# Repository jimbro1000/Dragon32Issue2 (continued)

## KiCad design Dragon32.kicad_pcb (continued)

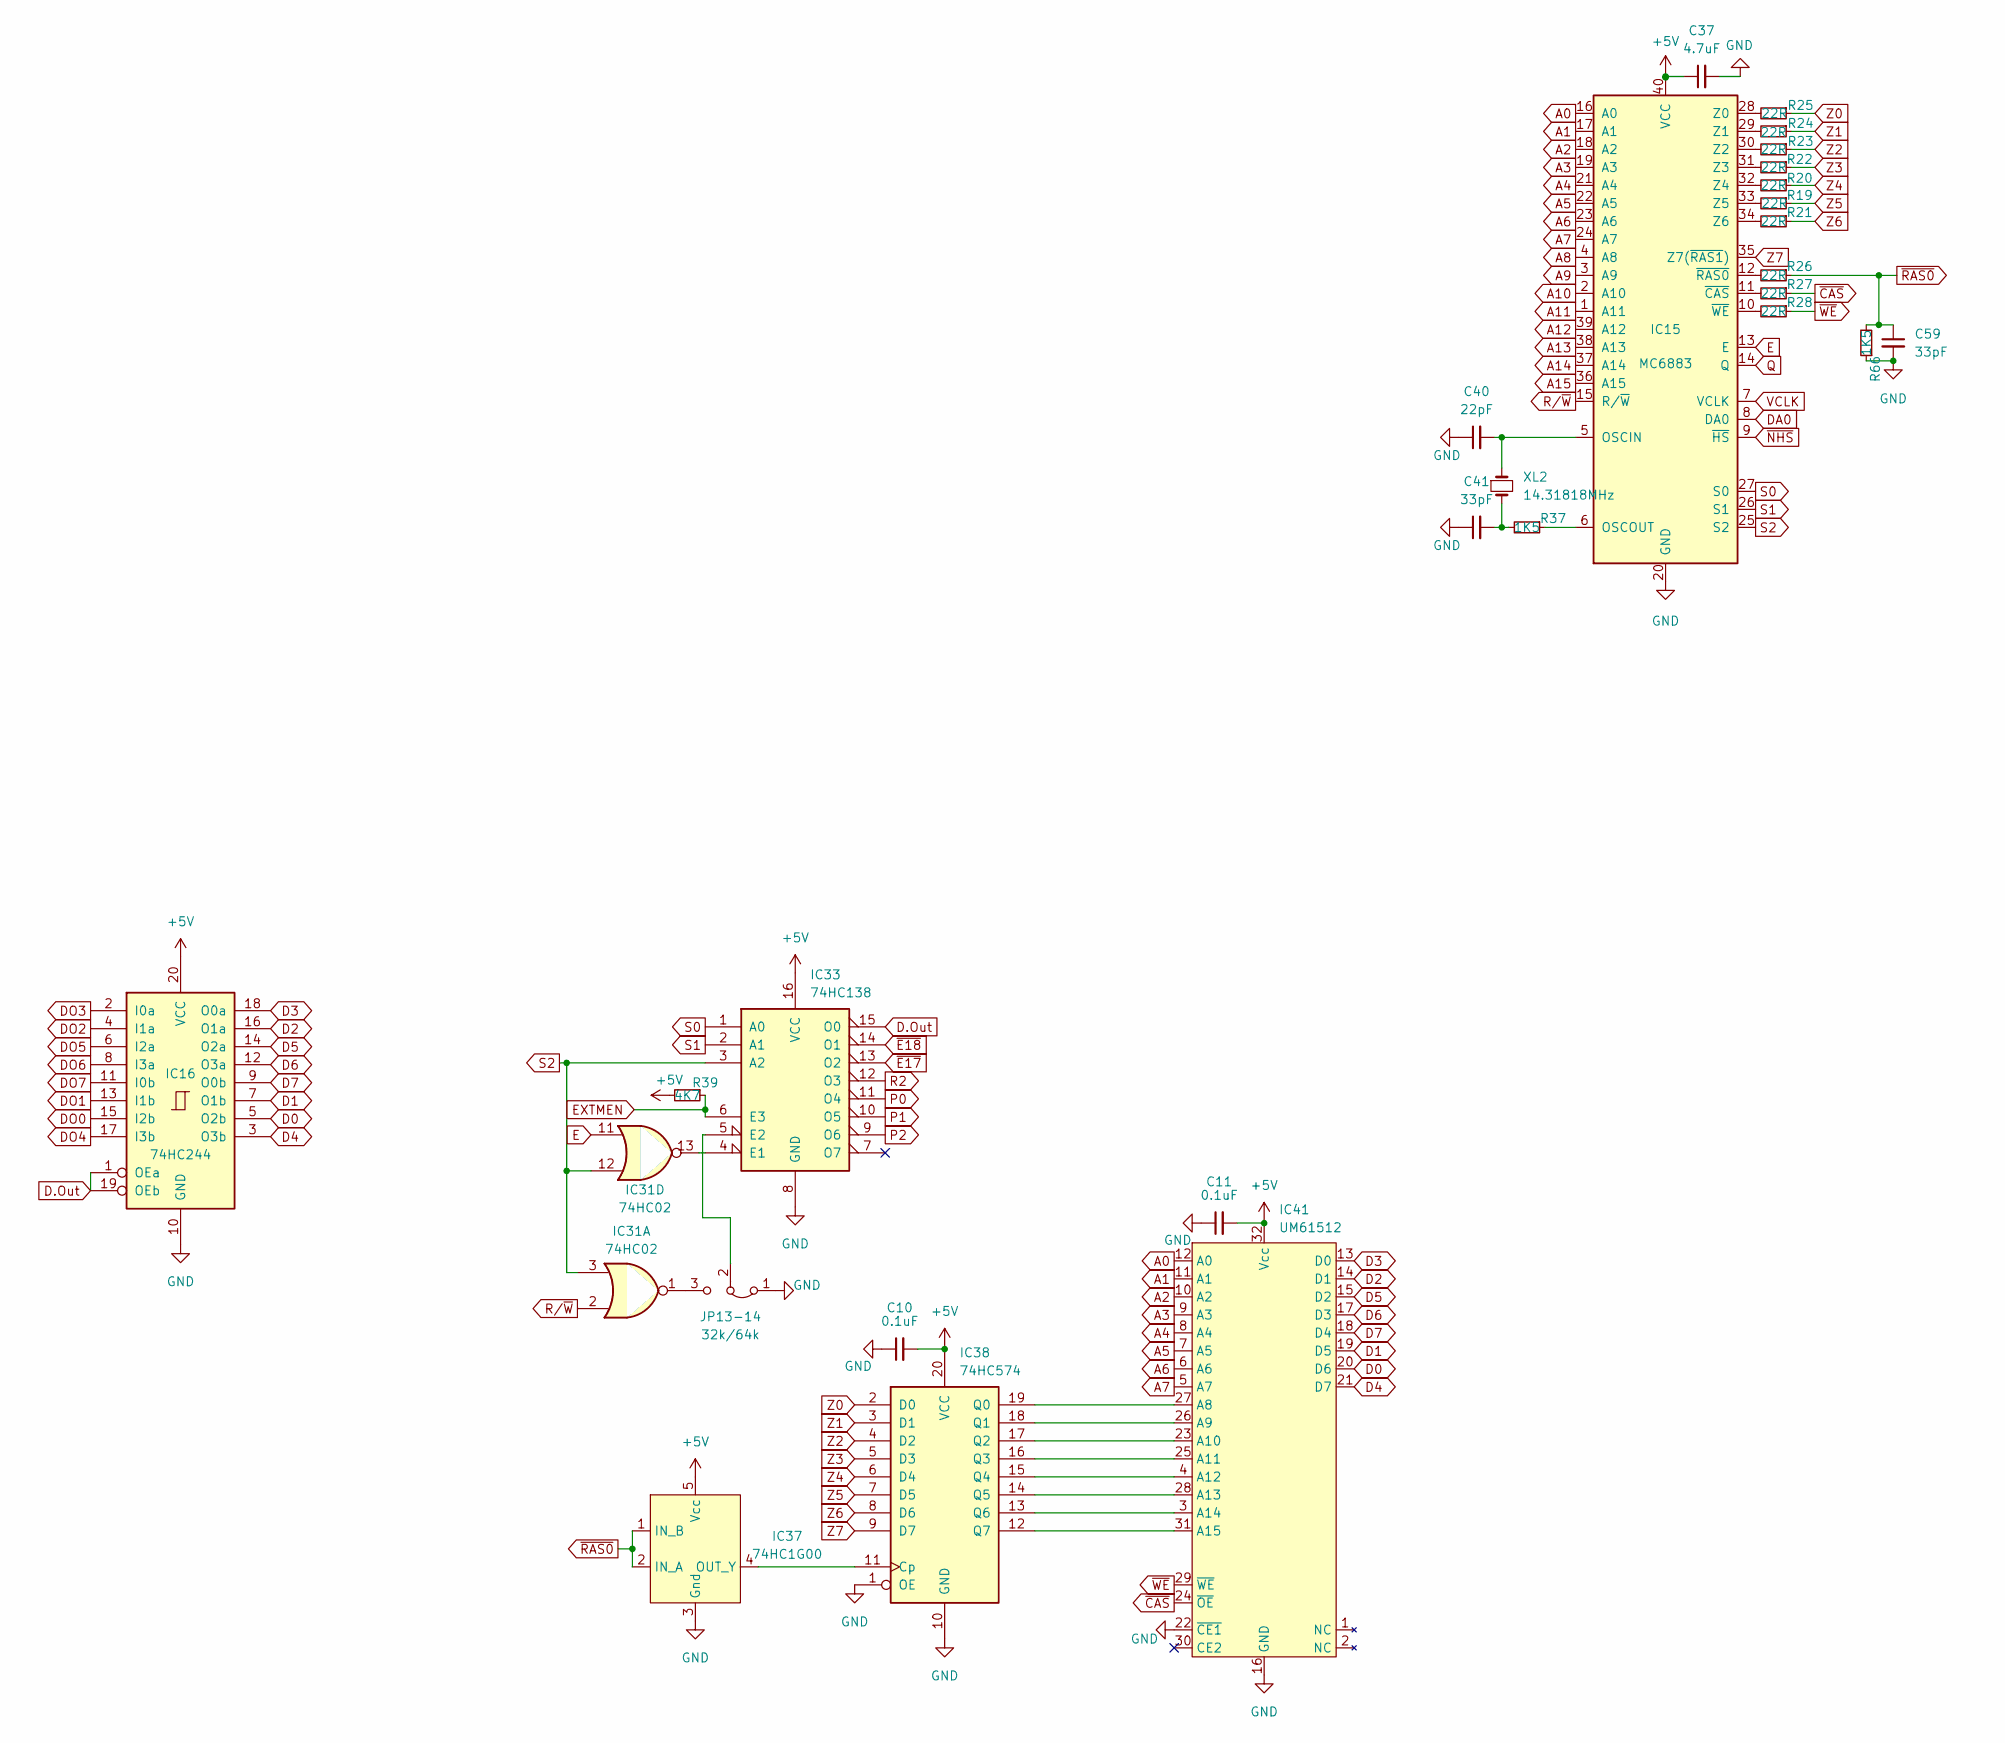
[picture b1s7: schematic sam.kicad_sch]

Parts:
C10, C11: 0.1uF; C_0805_2012Metric
C37: 4.7uF; C_0805_2012Metric
C40: 22pF; C_0805_2012Metric
C41, C59: 33pF; C_0805_2012Metric
IC15: MC6883; DIP-40_W15.24mm
IC16: 74HC244; SOIC-20W_7.5x12.8mm_P1.27mm
IC31: 74HC02; SOIC-14_3.9x8.7mm_P1.27mm
IC33: 74HC138; SOIC-16_3.9x9.9mm_P1.27mm
IC37: 74HC1G00; TSOP-5_1.65x3.05mm_P0.95mm
IC38: 74HC574; SOIC-20W_7.5x12.8mm_P1.27mm
IC41: UM61512; DIP-32_W7.62mm
JP13-14: 32k/64k; PinHeader_1x03_P2.54mm_Vertical
R19, R20, R21, R22, R23, R24, R25, R26, R27, R28: 22R; R_0805_2012Metric
R37, R66: 1K5; R_0805_2012Metric
R39: 4K7; R_0805_2012Metric
XL2: 14.31818MHz; Crystal_HC18-U_Horizontal

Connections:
+5V: C10.2, C11.2, C37.1, IC15.40 (VCC), IC16.20 (VCC), IC33.16 (VCC), IC37.5 (Vcc), IC38.20 (VCC), IC41.32 (Vcc), R39.2; also elsewhere on the board
A0: IC15.16 (A0), IC41.12 (A0); also elsewhere on the board
A1: IC15.17 (A1), IC41.11 (A1); also elsewhere on the board
A2: IC15.18 (A2), IC41.10 (A2); also elsewhere on the board
A3: IC15.19 (A3), IC41.9 (A3); also elsewhere on the board
A4: IC15.21 (A4), IC41.8 (A4); also elsewhere on the board
A5: IC15.22 (A5), IC41.7 (A5); also elsewhere on the board
A6: IC15.23 (A6), IC41.6 (A6); also elsewhere on the board
A7: IC15.24 (A7), IC41.5 (A7); also elsewhere on the board
A8: IC15.4 (A8); also elsewhere on the board
A9: IC15.3 (A9); also elsewhere on the board
A10: IC15.2 (A10); also elsewhere on the board
A11: IC15.1 (A11); also elsewhere on the board
A12: IC15.39 (A12); also elsewhere on the board
A13: IC15.38 (A13); also elsewhere on the board
A14: IC15.37 (A14); also elsewhere on the board
A15: IC15.36 (A15); also elsewhere on the board
D0: IC16.5 (O2b), IC41.20 (D6); also elsewhere on the board
D1: IC16.7 (O1b), IC41.19 (D5); also elsewhere on the board
D2: IC16.16 (O1a), IC41.14 (D1); also elsewhere on the board
D3: IC16.18 (O0a), IC41.13 (D0); also elsewhere on the board
D4: IC16.3 (O3b), IC41.21 (D7); also elsewhere on the board
D5: IC16.14 (O2a), IC41.15 (D2); also elsewhere on the board
D6: IC16.12 (O3a), IC41.17 (D3); also elsewhere on the board
D7: IC16.9 (O0b), IC41.18 (D4); also elsewhere on the board
D.Out: IC16.1 (OEa), IC16.19 (OEb), IC33.15 (O0)
DA0: IC15.8 (DA0); also elsewhere on the board
DO0: IC16.15 (I2b); also elsewhere on the board
DO1: IC16.13 (I1b); also elsewhere on the board
DO2: IC16.4 (I1a); also elsewhere on the board
DO3: IC16.2 (I0a); also elsewhere on the board
DO4: IC16.17 (I3b); also elsewhere on the board
DO5: IC16.6 (I2a); also elsewhere on the board
DO6: IC16.8 (I3a); also elsewhere on the board
DO7: IC16.11 (I0b); also elsewhere on the board
E: IC15.13 (E), IC31.11; also elsewhere on the board
EXTMEN: IC33.6 (E3), R39.1; also elsewhere on the board
GND: C10.1, C11.1, C37.2, C40.1, C41.1, C59.2, IC15.20 (GND), IC16.10 (GND), IC33.8 (GND), IC37.3 (Gnd), IC38.1 (OE), IC38.10 (GND), IC41.16 (GND), IC41.22 (~CE1), JP13-14.1 (A), R66.1; also elsewhere on the board
unnamed: C40.2, IC15.5 (OSCIN), XL2.1
unnamed: C41.2, R37.2, XL2.2
unnamed: IC15.6 (OSCOUT), R37.1
unnamed: IC15.10 (~WE), R28.2
unnamed: IC15.11 (~CAS), R27.2
unnamed: IC15.12 (~RAS0), R26.2
unnamed: IC15.28 (Z0), R25.2
unnamed: IC15.29 (Z1), R24.2
unnamed: IC15.30 (Z2), R23.2
unnamed: IC15.31 (Z3), R22.2
unnamed: IC15.32 (Z4), R20.2
unnamed: IC15.33 (Z5), R19.2
unnamed: IC15.34 (Z6), R21.2
unnamed: IC31.1, JP13-14.3 (B)
unnamed: IC31.13, IC33.4 (E1)
unnamed: IC33.5 (E2), JP13-14.2 (C)
unnamed: IC37.4 (OUT_Y), IC38.11 (Cp)
unnamed: IC38.12 (Q7), IC41.31 (A15)
unnamed: IC38.13 (Q6), IC41.3 (A14)
unnamed: IC38.14 (Q5), IC41.28 (A13)
unnamed: IC38.15 (Q4), IC41.4 (A12)
unnamed: IC38.16 (Q3), IC41.25 (A11)
unnamed: IC38.17 (Q2), IC41.23 (A10)
unnamed: IC38.18 (Q1), IC41.26 (A9)
unnamed: IC38.19 (Q0), IC41.27 (A8)
P0: IC33.11 (O4); also elsewhere on the board
P1: IC33.10 (O5); also elsewhere on the board
P2: IC33.9 (O6); also elsewhere on the board
Q: IC15.14 (Q); also elsewhere on the board
R2: IC33.12 (O3); also elsewhere on the board
R/~W: IC15.15 (R/~W), IC31.2; also elsewhere on the board
S0: IC15.27 (S0), IC33.1 (A0)
S1: IC15.26 (S1), IC33.2 (A1)
S2: IC15.25 (S2), IC31.3, IC31.12, IC33.3 (A2)
VCLK: IC15.7 (VCLK); also elsewhere on the board
Z0: IC38.2 (D0), R25.1
Z1: IC38.3 (D1), R24.1
Z2: IC38.4 (D2), R23.1
Z3: IC38.5 (D3), R22.1
Z4: IC38.6 (D4), R20.1
Z5: IC38.7 (D5), R19.1
Z6: IC38.8 (D6), R21.1
Z7: IC15.35 (Z7(~RAS1)), IC38.9 (D7)
~CAS: IC41.24 (~OE), R27.1
~E17: IC33.13 (O2); also elsewhere on the board
~E18: IC33.14 (O1); also elsewhere on the board
~NHS: IC15.9 (~HS); also elsewhere on the board
~RAS0: C59.1, IC37.1 (IN_B), IC37.2 (IN_A), R26.1, R66.2; also elsewhere on the board
~WE: IC41.29 (~WE), R28.1

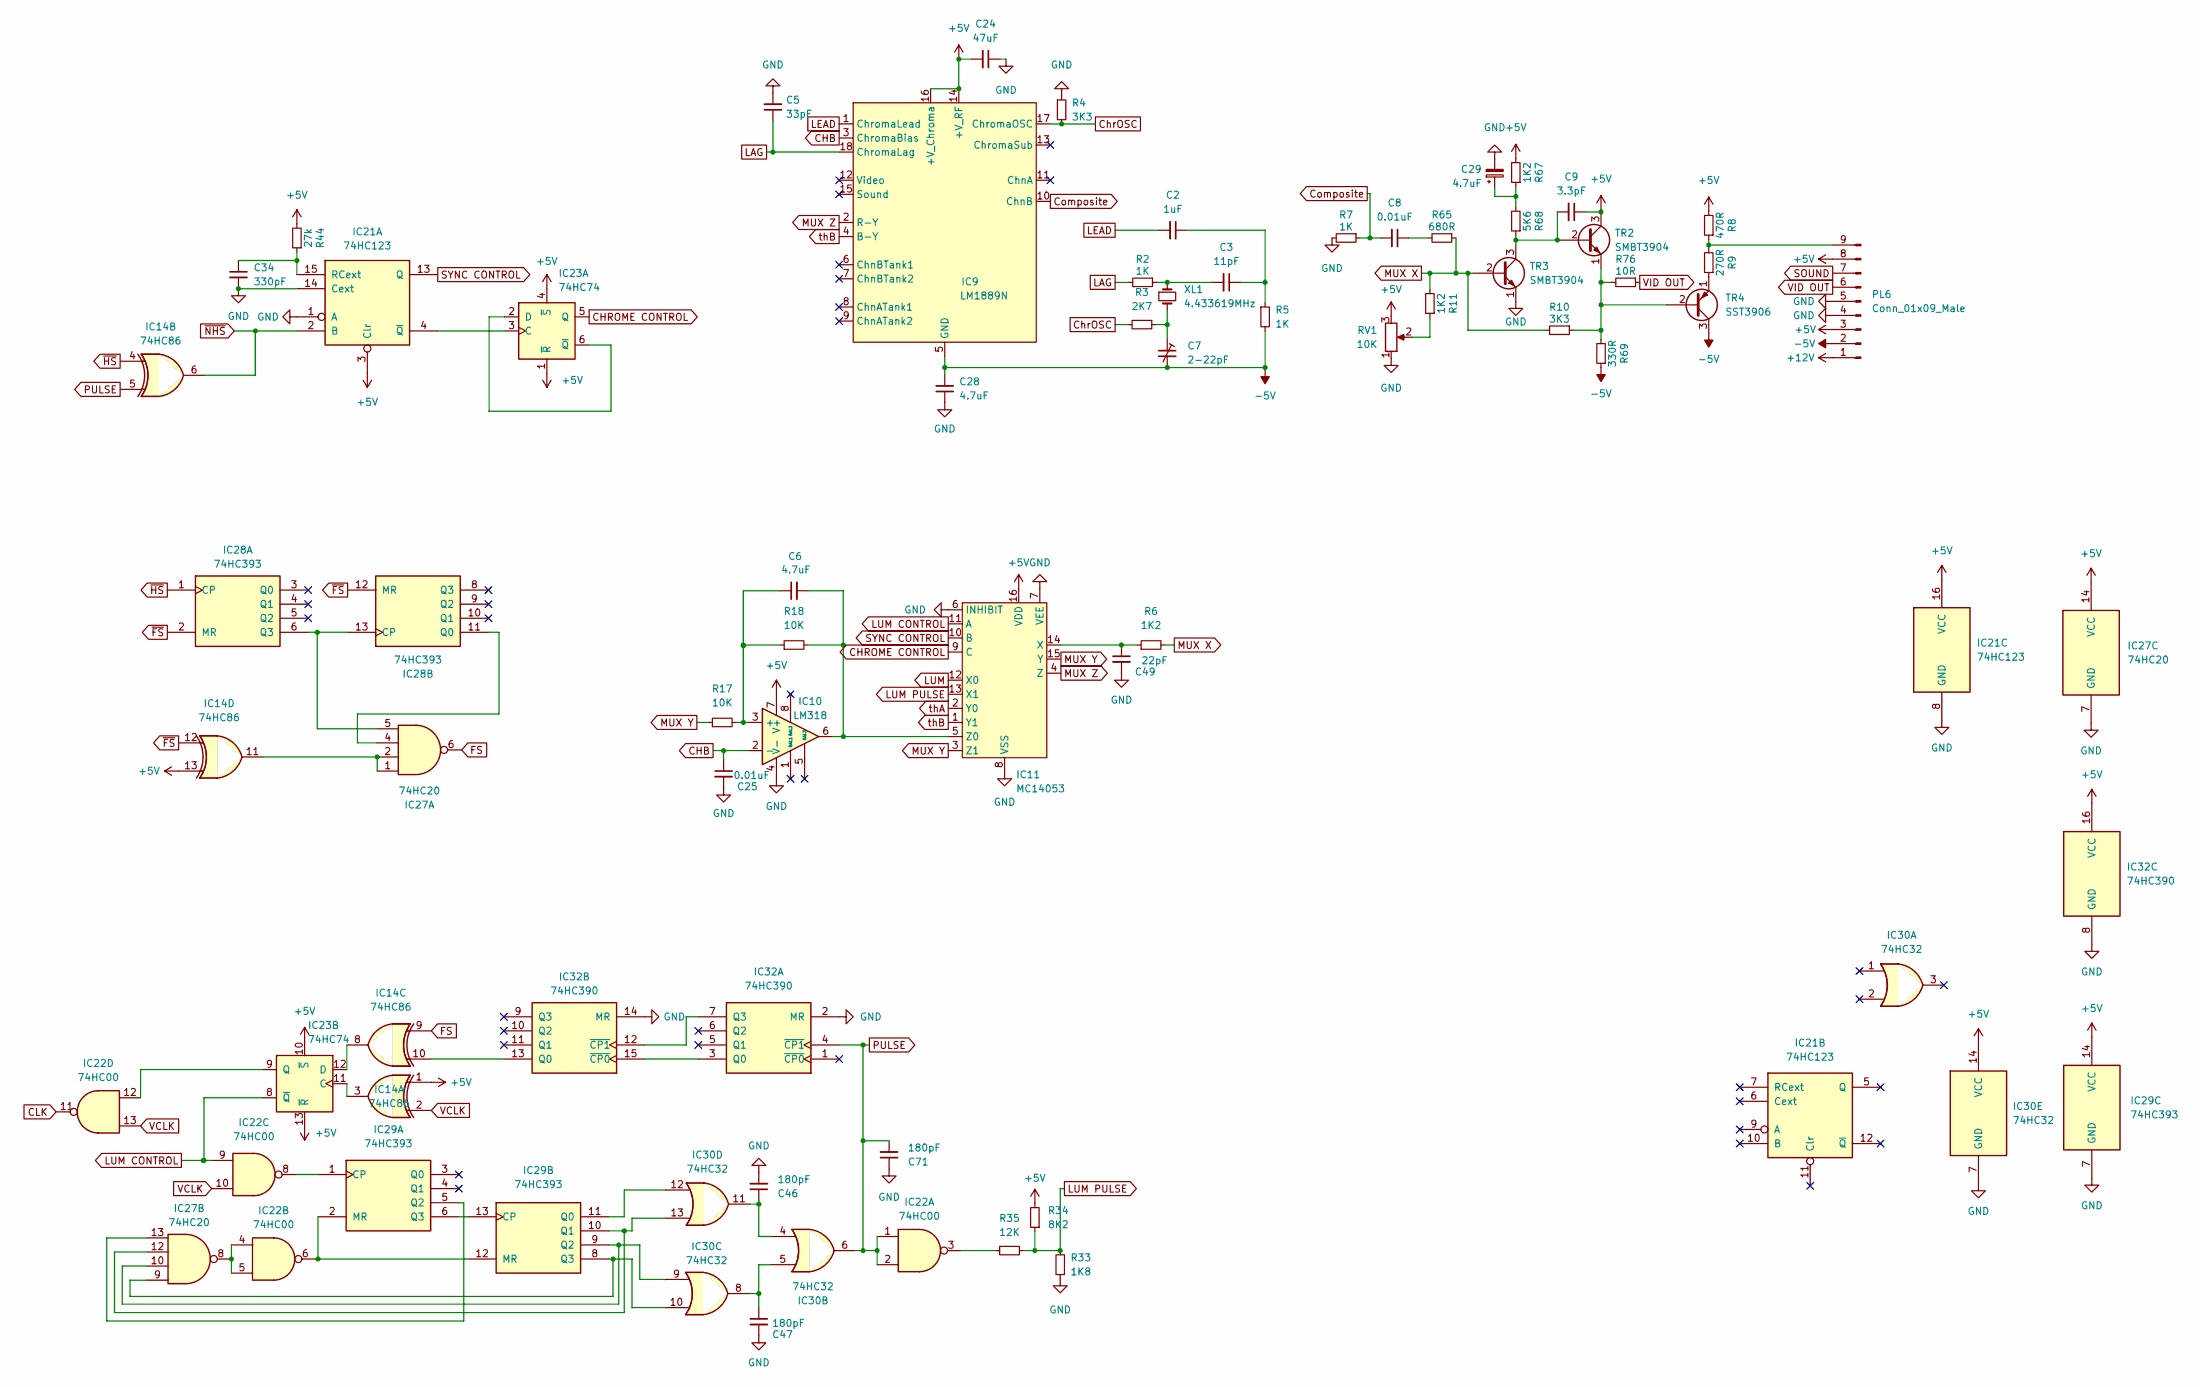
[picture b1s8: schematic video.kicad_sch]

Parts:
C2: 1uF; C_0805_2012Metric
C3: 11pF; C_0805_2012Metric
C5: 33pF; C_0805_2012Metric
C6, C28: 4.7uF; C_0805_2012Metric
C7: 2-22pF; Potentiometer_ACP_CA6-H2,5_Horizontal
C8, C25: 0.01uF; C_0805_2012Metric
C9: 3.3pF; C_0805_2012Metric
C24: 47uF; C_0805_2012Metric
C29: 4.7uF; CP_Elec_5x3
C34: 330pF; C_0805_2012Metric
C46, C47, C71: 180pF; C_0805_2012Metric
C49: 22pF; C_0805_2012Metric
IC9: LM1889N; DIP-18_W7.62mm
IC10: LM318; SOIC-8_3.9x4.9mm_P1.27mm
IC11: MC14053; SOIC-16_3.9x9.9mm_P1.27mm
IC14: 74HC86; SOIC-14_3.9x8.7mm_P1.27mm
IC21: 74HC123; SOIC-16_3.9x9.9mm_P1.27mm
IC22: 74HC00; SOIC-14_3.9x8.7mm_P1.27mm
IC23: 74HC74; SOIC-14_3.9x8.7mm_P1.27mm
IC27: 74HC20; SOIC-14_3.9x8.7mm_P1.27mm
IC28, IC29: 74HC393; SOIC-14_3.9x8.7mm_P1.27mm
IC30: 74HC32; SOIC-14_3.9x8.7mm_P1.27mm
IC32: 74HC390; SOIC-16_3.9x9.9mm_P1.27mm
PL6: Conn_01x09_Male; Molex_KK-396_A-41791-0009_1x09_P3.96mm_Vertical
R2, R5, R7: 1K; R_0805_2012Metric
R3: 2K7; R_0805_2012Metric
R4, R10: 3K3; R_0805_2012Metric
R6, R11, R67: 1K2; R_0805_2012Metric
R8: 470R; R_0805_2012Metric
R9: 270R; R_0805_2012Metric
R17, R18: 10K; R_0805_2012Metric
R33: 1K8; R_0805_2012Metric
R34: 8K2; R_0805_2012Metric
R35: 12K; R_0805_2012Metric
R44: 27k; R_0805_2012Metric
R65: 680R; R_0805_2012Metric
R68: 5K6; R_0805_2012Metric
R69: 330R; R_0805_2012Metric
R76: 10R; R_0805_2012Metric
RV1: 10K; Potentiometer_ACP_CA9-H5_Horizontal
TR2, TR3: SMBT3904; SOT-23
TR4: SST3906; SOT-23
XL1: 4.433619MHz; Crystal_HC18-U_Horizontal

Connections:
+5V: C9.1, C24.2, IC9.14 (+V_RF), IC9.16 (+V_Chroma), IC10.7 (V+), IC11.16 (VDD), IC14.1, IC14.13, IC21.3 (Clr), IC21.16 (VCC), IC23.1 (~R), IC23.4 (~S), IC23.10 (~S), IC23.13 (~R), IC27.14 (VCC), IC29.14 (VCC), IC30.14 (VCC), IC32.16 (VCC), PL6.3, PL6.8, R8.2, R34.2, R44.2, R67.2, RV1.3, TR2.3 (C); also elsewhere on the board
+12V: PL6.1; also elsewhere on the board
-5V: C7.2, C28.2, IC9.5 (GND), PL6.2, R5.2, R69.1, TR4.3 (C)
CHB: C25.1, IC9.3 (ChromaBias), IC10.2 (-); also elsewhere on the board
CHROME CONTROL: IC11.9 (C), IC23.5 (Q)
CLK: IC22.11; also elsewhere on the board
ChrOSC: IC9.17 (ChromaOSC), R3.2, R4.2
Composite: C8.2, IC9.10 (ChnB), R7.1
FS: IC14.9, IC27.6
GND: C5.2, C24.1, C25.2, C28.1, C29.2, C34.2, C46.2, C47.2, C49.2, C71.1, IC10.4 (V-), IC11.6 (INHIBIT), IC11.7 (VEE), IC11.8 (VSS), IC21.1 (A), IC21.8 (GND), IC21.14 (Cext), IC27.7 (GND), IC29.7 (GND), IC30.7 (GND), IC32.2 (MR), IC32.8 (GND), IC32.14 (MR), PL6.4, PL6.5, R4.1, R7.2, R33.1, RV1.1, TR3.1 (E); also elsewhere on the board
LAG: C5.1, IC9.18 (ChromaLag), R2.2
LEAD: C2.2, IC9.1 (ChromaLead)
LUM: IC11.12 (X0); also elsewhere on the board
LUM CONTROL: IC11.11 (A)
LUM PULSE: IC11.13 (X1), R33.2, R34.1, R35.1
MUX X: R6.2, R10.2, R11.2, R65.1, TR3.2 (B)
MUX Y: IC11.3 (Z1), IC11.15 (Y), R17.1
MUX Z: IC9.2 (R-Y), IC11.4 (Z)
unnamed: C2.1, C3.1, R5.1
unnamed: C3.2, R2.1, XL1.1
unnamed: C6.1, IC10.3 (+), R17.2, R18.1
unnamed: C6.2, IC10.6, IC11.5 (Z0), R18.2
unnamed: C7.1, R3.1, XL1.2
unnamed: C8.1, R65.2
unnamed: C9.2, R68.1, TR2.2 (B), TR3.3 (C)
unnamed: C29.1, R67.1, R68.2
unnamed: C34.1, IC21.15 (RCext), R44.1
unnamed: C46.1, IC30.4, IC30.11
unnamed: C47.1, IC30.5, IC30.8
unnamed: C49.1, IC11.14 (X), R6.1
unnamed: IC14.3, IC23.11 (C)
unnamed: IC14.8, IC23.12 (D)
unnamed: IC14.10, IC32.13 (Q0)
unnamed: IC14.11, IC27.1, IC27.2
unnamed: IC21.4 (~Q), IC23.3 (C)
unnamed: IC22.3, R35.2
unnamed: IC22.4, IC22.5, IC27.8
unnamed: IC22.6, IC29.2 (MR), IC29.12 (MR)
unnamed: IC22.8, IC29.1 (CP)
unnamed: IC22.9, IC23.8 (~Q)
unnamed: IC22.12, IC23.9 (Q)
unnamed: IC23.2 (D), IC23.6 (~Q)
unnamed: IC27.4, IC28.11 (Q0)
unnamed: IC27.5, IC28.6 (Q3), IC28.13 (CP)
unnamed: IC27.9, IC29.8 (Q3), IC30.10
unnamed: IC27.10, IC29.9 (Q2), IC30.9
unnamed: IC27.12, IC29.10 (Q1), IC30.13
unnamed: IC27.13, IC29.5 (Q2)
unnamed: IC29.11 (Q0), IC30.12
unnamed: IC29.6 (Q3), IC29.13 (CP)
unnamed: IC32.7 (Q3), IC32.12 (~CP1)
unnamed: IC32.3 (Q0), IC32.15 (~CP0)
unnamed: PL6.9, R8.1, R9.2
unnamed: R9.1, TR4.1 (E)
unnamed: R10.1, R69.2, R76.2, TR2.1 (E), TR4.2 (B)
unnamed: R11.1, RV1.2
PULSE: C71.2, IC14.5, IC22.1, IC22.2, IC30.6, IC32.4 (~CP1)
SOUND: PL6.7; also elsewhere on the board
SYNC CONTROL: IC11.10 (B), IC21.13 (Q)
VCLK: IC14.2, IC22.10, IC22.13; also elsewhere on the board
VID OUT: PL6.6, R76.1
thA: IC11.2 (Y0); also elsewhere on the board
thB: IC9.4 (B-Y), IC11.1 (Y1); also elsewhere on the board
~FS: IC14.12, IC28.2 (MR), IC28.12 (MR); also elsewhere on the board
~HS: IC14.4, IC28.1 (CP); also elsewhere on the board
~NHS: IC14.6, IC21.2 (B); also elsewhere on the board

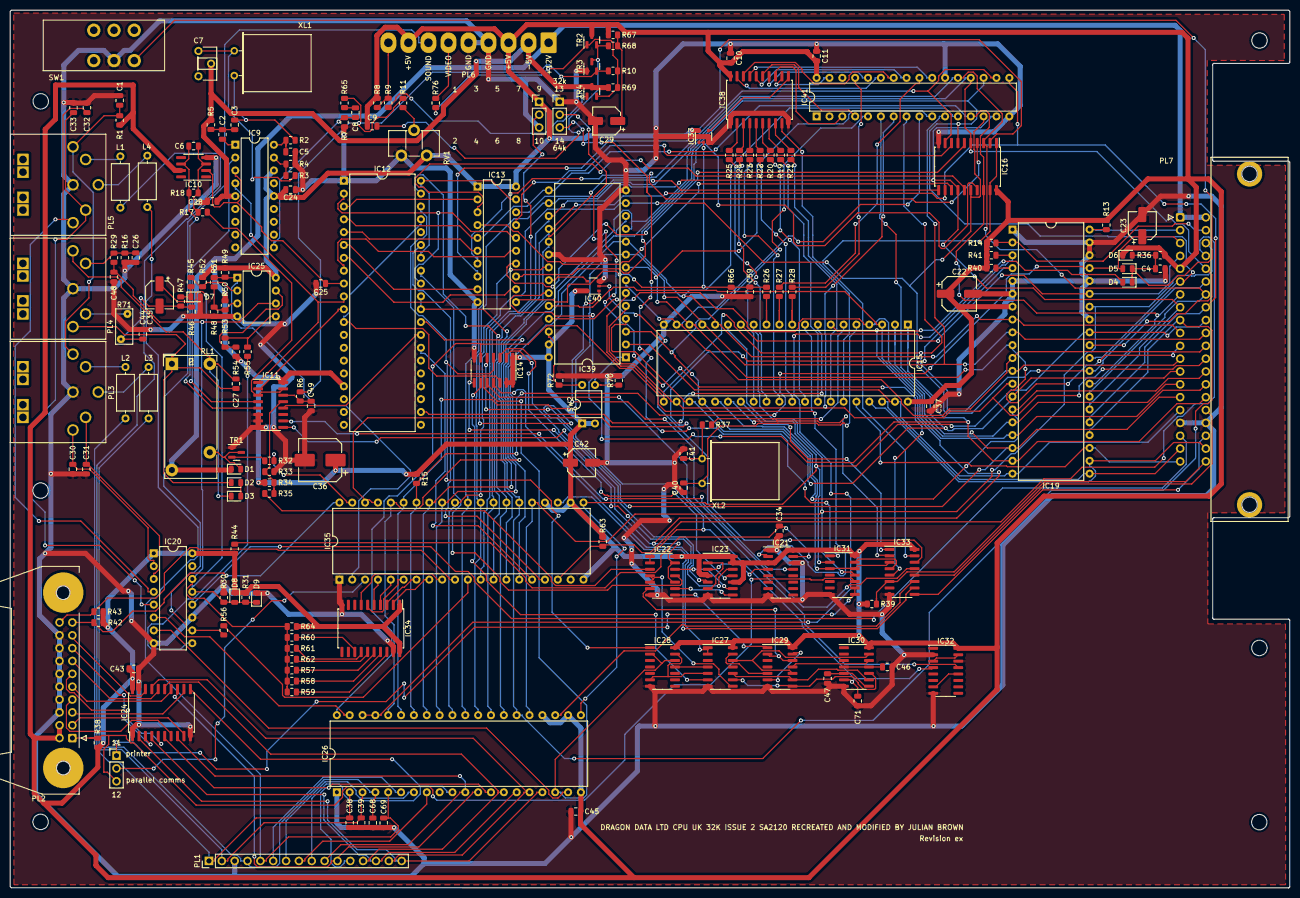
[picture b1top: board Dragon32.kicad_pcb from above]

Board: 2 copper layers, 252.9 x 173.5 mm, 178 parts (0 on the bottom side), 243 nets.

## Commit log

2022-09-25 add license
2022-09-25 fix board dimensions
2022-09-25 add drill holes
2022-09-25 resolve conflicts
2022-09-25 update drawings
2022-09-25 add readme
2022-09-26 add 64k switch
2022-09-26 tidy up pcb
2022-09-26 update interactive bom
2022-09-26 update simple bom
2022-09-26 add jumper 5 (position 9 and 10)
2022-09-26 update notes
2022-09-26 convert to smd
2022-09-27 autoroute board
2022-09-28 complete wiring
2022-09-28 update page settings
2022-09-28 fix footprint of IC33
2022-09-29 swap new and gate over to a single circuit chip
2022-09-29 convert memory to sram
2022-09-30 relocate dram and buffer to match original
2022-10-11 prepare board for drill hole fix
2022-10-12 revise edge connector
2022-10-12 validate component values
2022-10-12 resitor values pt1
2022-10-12 add changelog
2022-10-13 complete component revision
2022-10-13 cross-reference items to suppliers
2022-10-14 update part numbers
2022-10-14 update bom
2022-10-14 provide renders of the board
2022-10-15 resolve part numbers
2022-10-15 beautify the board
2022-10-15 fix broken PIA2 to multiplexer line
2022-10-15 record changes
2022-10-15 label pins
2022-10-15 label cartridge pins
2022-10-16 fix video circuit gnd
2022-10-16 redraw video schematic for clarity
2022-10-16 fix link IC25 to IC26
2022-10-17 fix edge connector and op-amp
2022-10-18 refresh pcb
2022-10-19 fix relay footprint
2022-10-21 update pcb
2022-10-28 fix typo on 6833 silkscreen
2022-10-30 respace traces
2022-10-31 revise power connector labels
2022-11-01 improve trace separation
2022-11-01 add mechanical tie points for large crystals
2022-11-01 add bypass for secondary video amp
2022-11-07 improve trace clearance
2022-11-07 rewire 5v lines
2022-11-08 prepare for release of rev 1.5
2022-11-08 update silkscreen
2022-11-08 improve layout
2022-12-08 improve 12v routes
2022-12-20 verify video logic
2022-12-21 fix line pulse counter ic32
2022-12-27 reroute video circuit
2023-01-03 reroute power
2023-01-03 changes to compare
2023-01-03 tidy up
2023-01-04 rationalise cpu data lines
2023-01-05 update changelog
2023-01-06 improve ram zone groundplane
2023-01-06 tidyup routing
2023-01-06 general update
2023-01-06 rework RV3
2023-01-06 move C42 to more appropriate position
2023-01-07 update capacitor values for joystick button input
2023-01-08 add trace labels for joysticks
2023-01-08 fix +v rail on IC25 comparator
2023-01-08 update dcumentation
2023-01-08 fix dac
2023-01-09 review line counter
2023-01-12 improve annotation of dac
2023-01-12 provide on board annotation of dac
2023-01-13 rewire relay position
2023-01-13 refine 12v trace
2023-01-14 revise component values
2023-01-14 update documents
2023-01-14 Revert "improve trace clearance"
    This reverts commit 3cf644d67ec5c70c51931af734b43aed31f61206.
2023-01-27 fix voltage wiring
2023-01-27 add change notes
2023-02-10 fix c7 footprint
2023-02-14 fix rv3
2023-02-14 upgrade to kicad 7
2023-02-18 fix chroma output from IC9
2023-02-18 fix inputs to video amp
2023-02-22 fix video amp cap value
2023-02-22 remove autoroute files
2023-05-09 revise video circuit
2023-05-10 Update component values
2023-05-10 Refine schematic detail and pcb traces
2023-05-10 fix vs code butchering of schematics
2023-05-14 repair damaged pcb definition
2023-05-20 Update README.md
    Report video circuit working
2023-05-20 annotate video schematic
2023-06-03 add ntsc config
2023-06-03 increase revision
2023-06-03 fix drc error
2023-06-03 add video pickup
2023-06-10 fix diff amp wiring
2023-06-13 refill ground
2023-06-24 optimise traces
2023-07-11 re-generate for updated DRC fix
2023-08-11 revise bom
2023-09-11 provide build instructions
2023-11-04 improve build support notes
2025-08-28 update bom references
2025-11-11 fix parallel strobe inverter bypass
2025-11-13 note error recorded on rev22
2025-11-13 update renders
